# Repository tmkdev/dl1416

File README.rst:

======
dl1416
======

Library for driving DL1416/DL2416 LED arrays on Raspberry Pi/RPi.GPIO supported dev boards

Installation
============

pip install dl1416

Example Usage
=============

from dl1416 import DL1416

dl = DL1416()    

dl.initdisplay()
dl.clear()

dl.writestring('HELO')

Hardware Config
===============

DL1416 default pin connections

(Using BOARD pin numbers)

Altenate pins can be passed into the constructor

D6,D5,D4,D3,D2,D1,D0
datapins = [19, 15, 13, 11, 7, 5, 3]

A1,A0
addresspins = [18, 16]

ce = 22

wr = 24

cu = 26

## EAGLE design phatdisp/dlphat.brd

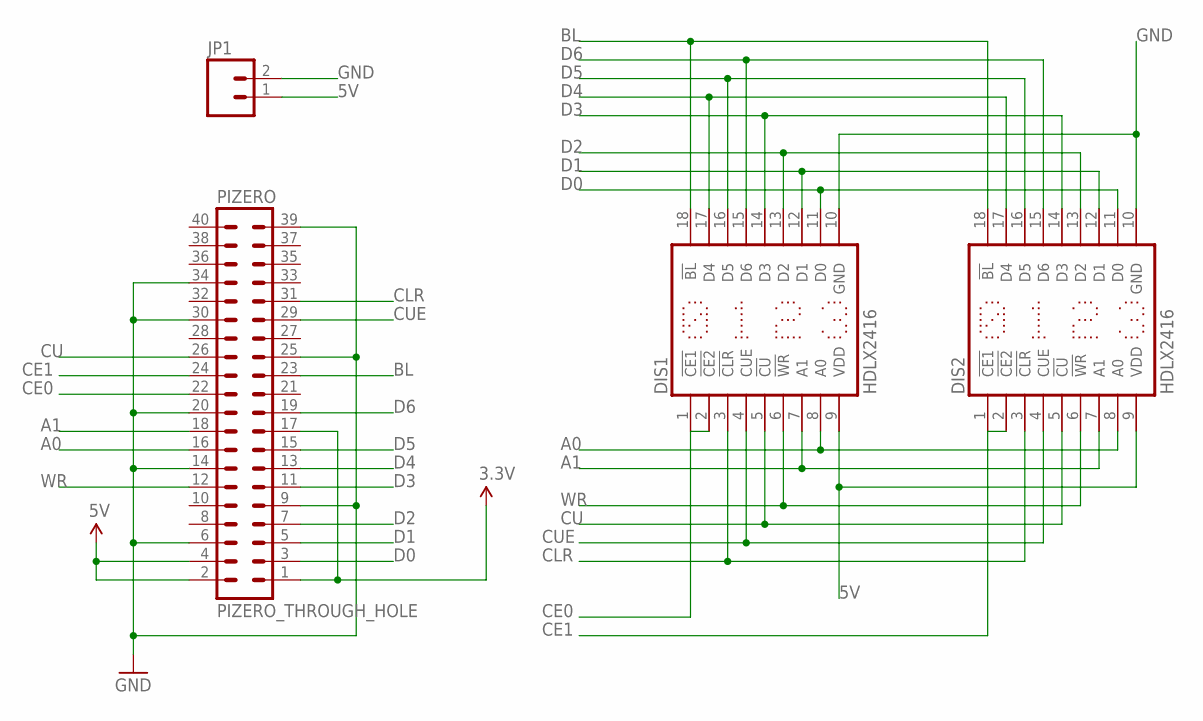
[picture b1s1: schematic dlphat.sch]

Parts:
DIS1, DIS2: HDLX2416
JP1: M02POLAR; MOLEX-1X2
PIZERO: PIZERO_THROUGH_HOLE; PIZERO_THOUGH_HOLE

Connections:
3.3V: PIZERO.1, PIZERO.17
5V: DIS1.9 (VDD), DIS2.9 (VDD), JP1.1, PIZERO.2, PIZERO.4
A0: DIS1.8 (A0), DIS2.8 (A0), PIZERO.16
A1: DIS1.7 (A1), DIS2.7 (A1), PIZERO.18
BL: DIS1.18 (!BL), DIS2.18 (!BL), PIZERO.23
CE0: DIS1.1 (!CE1), DIS1.2 (!CE2), PIZERO.22
CE1: DIS2.1 (!CE1), DIS2.2 (!CE2), PIZERO.24
CLR: DIS1.3 (!CLR), DIS2.3 (!CLR), PIZERO.31
CU: DIS1.5 (!CU), DIS2.5 (!CU), PIZERO.26
CUE: DIS1.4 (CUE), DIS2.4 (CUE), PIZERO.29
D0: DIS1.11 (D0), DIS2.11 (D0), PIZERO.3
D1: DIS1.12 (D1), DIS2.12 (D1), PIZERO.5
D2: DIS1.13 (D2), DIS2.13 (D2), PIZERO.7
D3: DIS1.14 (D3), DIS2.14 (D3), PIZERO.11
D4: DIS1.17 (D4), DIS2.17 (D4), PIZERO.13
D5: DIS1.16 (D5), DIS2.16 (D5), PIZERO.15
D6: DIS1.15 (D6), DIS2.15 (D6), PIZERO.19
GND: DIS1.10 (GND), DIS2.10 (GND), JP1.2, PIZERO.6, PIZERO.9, PIZERO.14, PIZERO.20, PIZERO.25, PIZERO.30, PIZERO.34, PIZERO.39
WR: DIS1.6 (!WR), DIS2.6 (!WR), PIZERO.12

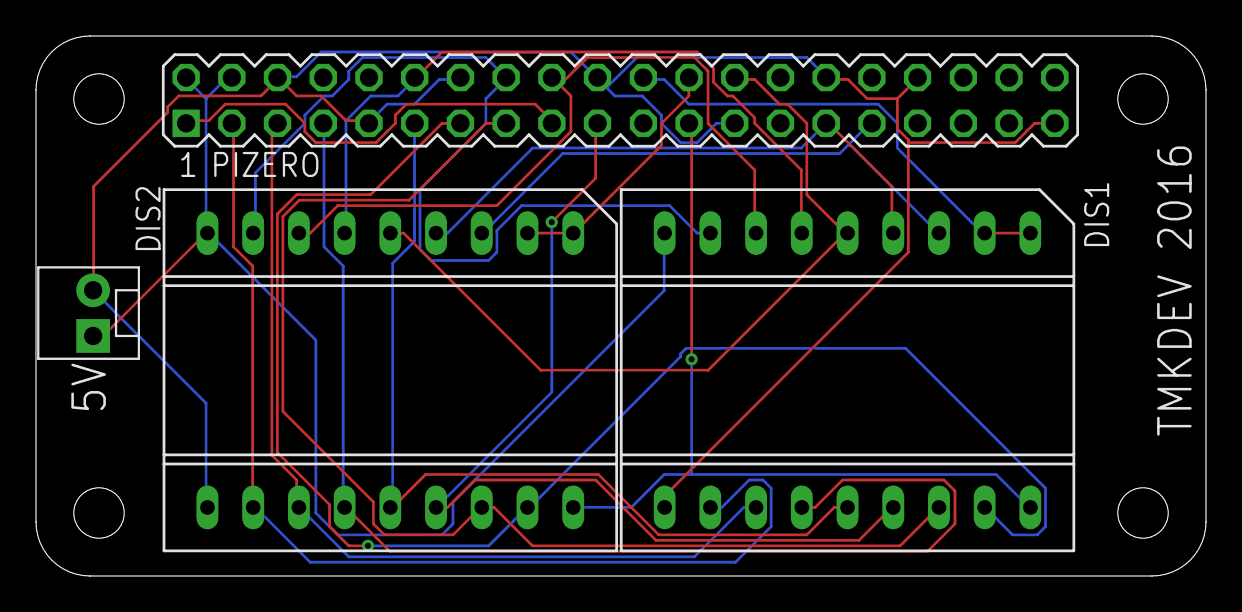
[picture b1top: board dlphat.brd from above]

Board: 2 copper layers, 65.0 x 30.0 mm, 4 parts (0 on the bottom side), 19 nets.

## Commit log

2016-10-09 Updated git URL
2016-10-09 Added LICENCE
2016-10-09 README typos
2016-10-09 Renamed LICENSE
2016-10-09 Clarification on PIN defs
2016-11-05 Refactored and added support for dual displays
2016-11-05 Bump in version
2016-11-16 Closer to working final project
2016-11-16 Added phatdisp PCB design files

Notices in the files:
parts and their libraries:
SparkFun-Connectors: Licensing: Creative Commons ShareAlike 4.0 International - https://creativecommons.org/licenses/by-sa/4.0
